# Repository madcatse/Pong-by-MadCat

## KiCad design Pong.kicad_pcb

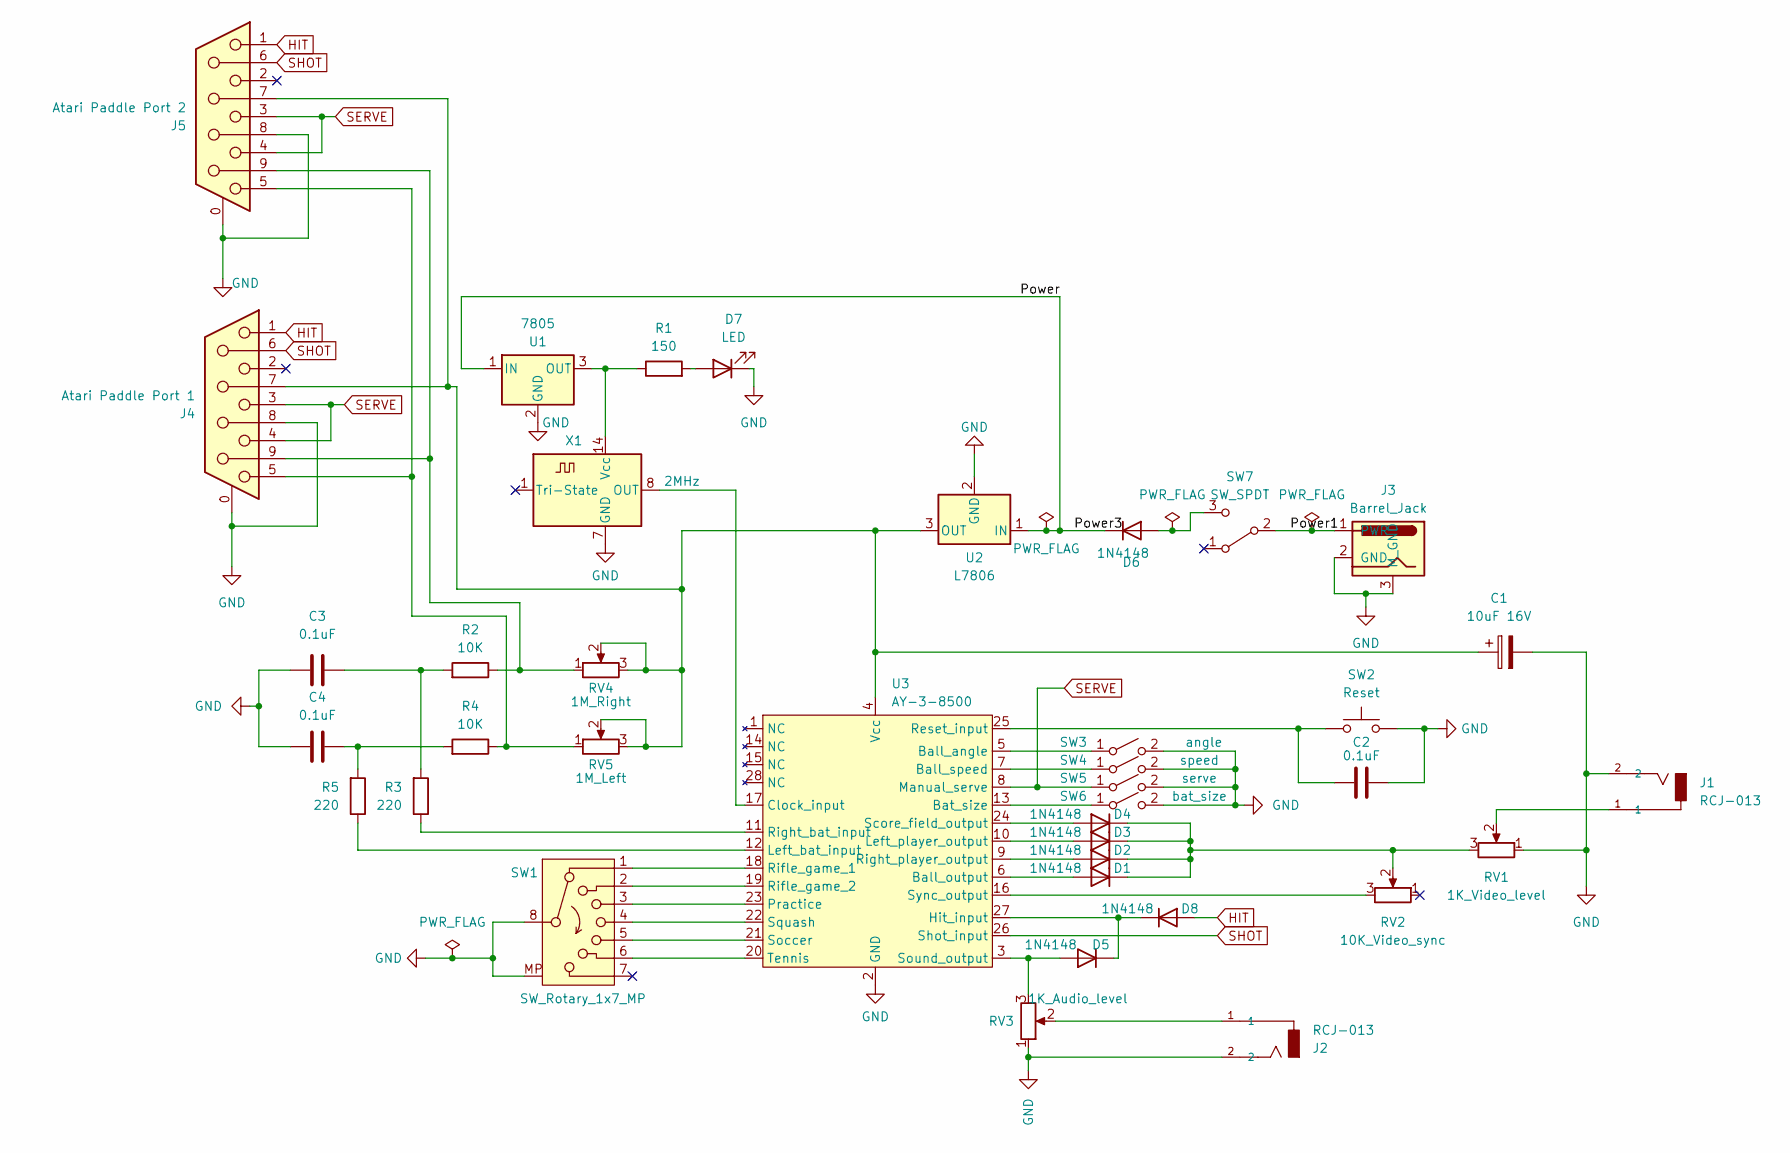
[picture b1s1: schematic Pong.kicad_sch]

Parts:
C1: 10uF 16V; CP_Radial_D4.0mm_P1.50mm
C2, C3, C4: 0.1uF; C_Disc_D4.3mm_W1.9mm_P5.00mm
D1, D2, D3, D4, D5, D6, D8: 1N4148; D_DO-35_SOD27_P10.16mm_Horizontal
D7: LED; PinHeader_1x02_P2.54mm_Vertical
J1, J2: RCJ-013; AV
J3: Barrel_Jack; BarrelJack_GCT_DCJ200-10-A_Horizontal
J4: Atari Paddle Port 1; DSUB-9_Female_Horizontal_P2.77x2.84mm_EdgePinOffset4.94mm_H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
J5: Atari Paddle Port 2; DSUB-9_Female_Horizontal_P2.77x2.84mm_EdgePinOffset4.94mm_H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
R1: 150; R_Axial_DIN0207_L6.3mm_D2.5mm_P10.16mm_Horizontal
R2, R4: 10K; R_Axial_DIN0207_L6.3mm_D2.5mm_P10.16mm_Horizontal
R3, R5: 220; R_Axial_DIN0207_L6.3mm_D2.5mm_P10.16mm_Horizontal
RV1: 1K_Video_level; Potentiometer_Bourns_3006P_Horizontal
RV2: 10K_Video_sync; Potentiometer_Bourns_3006P_Horizontal
RV3: 1K_Audio_level; Potentiometer_Bourns_3006P_Horizontal
RV4: 1M_Right; PinHeader_1x03_P2.54mm_Vertical
RV5: 1M_Left; PinHeader_1x03_P2.54mm_Vertical
SW1: SW_Rotary_1x7_MP; game_selector
SW2: Reset; PinHeader_1x02_P2.54mm_Vertical
SW3: angle; PinHeader_1x02_P2.54mm_Vertical
SW4: speed; PinHeader_1x02_P2.54mm_Vertical
SW5: serve; PinHeader_1x02_P2.54mm_Vertical
SW6: bat_size; PinHeader_1x02_P2.54mm_Vertical
SW7: SW_SPDT; pwr_switch
U1: 7805; TO-220-3_Horizontal_TabDown
U2: L7806; TO-220-3_Horizontal_TabDown
U3: AY-3-8500; DIP-28_W15.24mm
X1: 2MHz; Oscillator_DIP-14

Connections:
/Power: D6.1 (K), U1.1 (IN), U2.1 (IN)
/Power1: J3.1 (PWR), SW7.2 (B)
GND: C1.2, C2.1, C3.2, C4.2, D7.1 (K), J1.2, J2.2, J3.2 (GND), J3.3 (M_GND), J4.0 (PAD), J4.8, J5.0 (PAD), J5.8, RV1.1, RV3.1, SW1.8, SW1.MP, SW2.2, SW3.2 (B), SW4.2 (B), SW5.2 (B), SW6.2 (B), U1.2 (GND), U2.2 (GND), U3.2 (GND), X1.7 (GND)
HIT: D8.2 (A), J4.1, J5.1
unnamed: C3.1, R2.2, R3.2
unnamed: C4.1, R4.2, R5.2
unnamed: D1.2 (A), U3.6 (Ball_output)
unnamed: D1.1 (K), D2.1 (K), D3.1 (K), D4.1 (K), RV1.3, RV2.2
unnamed: D2.2 (A), U3.9 (Right_player_output)
unnamed: D3.2 (A), U3.10 (Left_player_output)
unnamed: D4.2 (A), U3.24 (Score_field_output)
unnamed: D5.2 (A), RV3.3, U3.3 (Sound_output)
unnamed: D5.1 (K), D8.1 (K), U3.27 (Hit_input)
unnamed: D6.2 (A), SW7.3 (C)
unnamed: D7.2 (A), R1.2
unnamed: J1.1, RV1.2
unnamed: J2.1, RV3.2
unnamed: J4.5, J5.5, R4.1, RV5.1
unnamed: J4.9, J5.9, R2.1, RV4.1
unnamed: SW3.1 (A), U3.5 (Ball_angle)
unnamed: SW4.1 (A), U3.7 (Ball_speed)
unnamed: SW6.1 (A), U3.13 (Bat_size)
unnamed: R1.1, U1.3 (OUT), X1.14 (Vcc)
unnamed: C1.1, J4.7, J5.7, RV4.2, RV4.3, RV5.2, RV5.3, U2.3 (OUT), U3.4 (Vcc)
unnamed: U3.17 (Clock_input), X1.8 (OUT)
unnamed: R5.1, U3.12 (Left_bat_input)
unnamed: SW1.3, U3.23 (Practice)
unnamed: C2.2, SW2.1, U3.25 (Reset_input)
unnamed: SW1.1, U3.18 (Rifle_game_1)
unnamed: SW1.2, U3.19 (Rifle_game_2)
unnamed: R3.1, U3.11 (Right_bat_input)
unnamed: SW1.5, U3.21 (Soccer)
unnamed: SW1.4, U3.22 (Squash)
unnamed: RV2.3, U3.16 (Sync_output)
unnamed: SW1.6, U3.20 (Tennis)
SERVE: J4.3, J4.4, J5.3, J5.4, SW5.1 (A), U3.8 (Manual_serve)
SHOT: J4.6, J5.6, U3.26 (Shot_input)

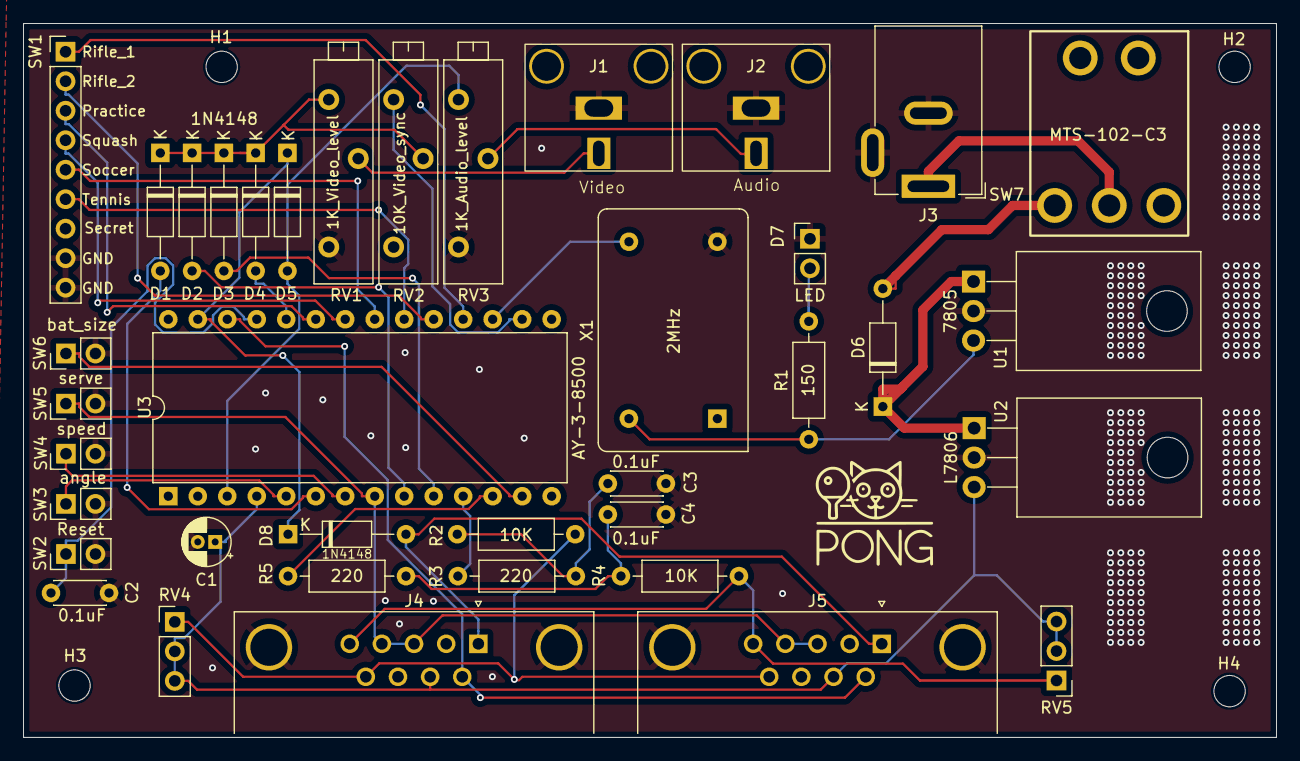
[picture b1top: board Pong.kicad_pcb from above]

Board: 2 copper layers, 107.9 x 61.5 mm, 43 parts (0 on the bottom side), 37 nets.

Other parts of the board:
G1: LOGO; catpong
H1, H2, H3, H4: MountingHole_2.7mm_M2.5

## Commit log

2025-01-28 Initial Upload
2025-01-28 Gerbers
2026-05-26 Cleanup
